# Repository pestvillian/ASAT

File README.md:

**Automated Sample Agitation Transportation System**

We are an Electrical Engineering Capstone group from the University of California, Santa Cruz. Our project aims to design a more efficient, more cost-effective solution for medical staff and researchers to process human samples for imaging. 

Here is an overview of the file structure:
  - Five folders for each group member
  - "Motor-Controller-Firmware" Firmware files for the motor controller motherboard and touchscreen daughterboard
  - "Motor-Controller-Board" contains PCB files for the Motor Controller PCB
  - "motor_tests" has test scripts for controlling the motors

Finally, we created a poster to visually explain our project!

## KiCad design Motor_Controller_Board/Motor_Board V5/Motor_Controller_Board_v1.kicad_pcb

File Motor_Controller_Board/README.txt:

List of changes to track progress.

4/17/25 9:55pm. Added TMC2226 stepper driver to schematic and followed the datasheet. left questions in the schematic. main concerns are vmotor filtering, do we need diagnostic pins like pdn_uart, diag and index, and what vsense resistors do we use? there are other smaller questions too. -Dorjee

4/17/25 11:42pm. made some small updates. vmotor basic filtering is two 100n decouple caps and one 100u bulk cap. they recommend low ESR caps, which provide faster response time. however, they also recommend voltage spikes to be delayed, which would imply high ESR caps would be good too? need to do more research

4/30/25. schematic rough draft is done. i need to revisions now to make sure it will actually work. there is a main page, buck page, microcontroller page, and a stepper driver page. 

5/2/25. revised schematic with Mishari and Alex. pretty confident in the design, so we started picking footprints. I've finished the microcontroller and stepper driver footprints, working on the buck regulators right now. i want to use the same 50V rated capacitor for both Cin and Cout.

5/3/25. all footprints assigned and every part manufacturer, manufacturer part number, and jcsc part number for BOM. added boot configuration for microcontroller. ready to begin premature layout, but still very open to changes in schematic.

5/3/25. added all 3d models and starting pcb layout. it is tricky

5/4/25. drastically simplified design by using 24V from SMPS for all motors. only one buck regulator for logic components. layout has begun and a general placement for parts has been established by myself without review from team yet. many changes can be made. stepper drivers likely will switch to +3.3V logic, vmotor filtering should be changed to surface mounts for size continuity, copy pasting the setup from one driver to the other two, and more. 

5/5/25. Reviewed schematic with Alex and Mishari. We are confident in the schematic, we will clean up a few last things tonight and then continue layout tomorrow.

5/5/25. placed all components in a rough outline, going to review with teammates tomorrow.

5/6/25. 75% of routing finished, but the routing was very sloppy.

5/7/25. pcb design is almost finished. Petersen was relatively happy with our layout and gave some tips. mishari will implement the tips tonight. no erc or drc errors currently except for the asats logo on the pcb layout. needs a final review tomorrow and then it will be ordered!

5/8/25. Mishari added bottom +24V plane instead of 2mm trace and was reviewed by team. Changed enable pins to be controlled by esp32. added potentiometer. alex, mishari and Dorjee all reviewed footprints and design. we plan to order tomorrow, will review tonight and tomorrow before ordering.

5/8/25. switched board to horizontal text and cleaned it up.

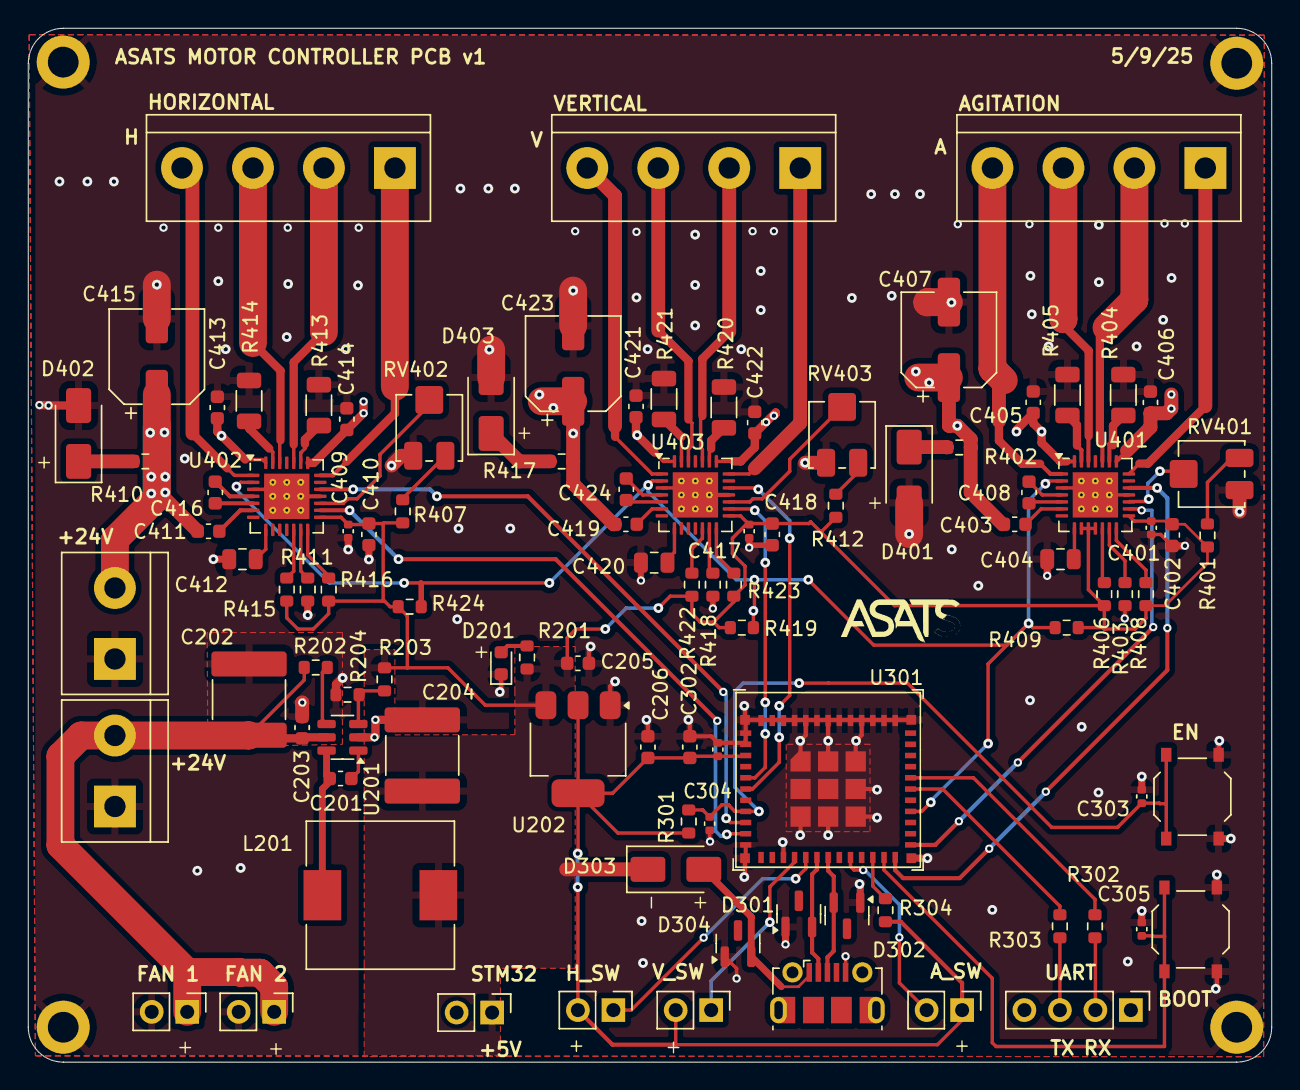
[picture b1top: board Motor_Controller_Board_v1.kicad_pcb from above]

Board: 2 copper layers, 89.0 x 74.0 mm, 104 parts (0 on the bottom side), 78 nets.

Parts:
C201, C203, C403, C405, C406, C408, C411, C413, C414, C416, C419, C421, C422, C424: 100n; C_0603_1608Metric
C202, C204: 22u; C_2220_5750Metric
C205, C206, C302, C402, C410, C418: 10u; C_0603_1608Metric
C301, C303, C305, C401, C409, C417: 100n; C_0402_1005Metric
C304: 1u; C_0402_1005Metric
C404, C412, C420: 220n; C_0805_2012Metric
C407, C415, C423: 100u; CP_Elec_6.3x7.7
D201: RED; LED_0603_1608Metric
D301, D302, D304: PSM712-LF-T7; SOT-23
D303: SS14; D_SMA
D401, D402, D403: SMAJ28A; D_SMA
H201, H202, H203, H204: MountingHole_Pad; MountingHole_2.2mm_M2_DIN965_Pad
J201, J203: Conn_01x02; TerminalBlock_bornier-2_P5.08mm
J202, J206, J207, J303, J304, J305: Conn_01x02; PinHeader_1x02_P2.54mm_Vertical
J301: Conn_01x04; PinHeader_1x04_P2.54mm_Vertical
J302: USB_B_Micro; USB_Micro-B_Molex-105017-0001
J401, J402, J403: Conn_01x04; TerminalBlock_bornier-4_P5.08mm
L201: 22u; L_10.4x10.4_H4.8
R201: 5k1; R_0603_1608Metric
R202, R408, R409, R416, R419, R423, R424: 100k; R_0603_1608Metric
R203: 68k; R_0603_1608Metric
R204: 13k; R_0603_1608Metric
R301, R304, R406, R415, R422: 10k; R_0603_1608Metric
R302, R303: 0R; R_0603_1608Metric
R401, R403, R407, R411, R412, R418: 24k; R_0603_1608Metric
R402, R410, R417: 10R; R_0603_1608Metric
R404, R405, R413, R414, R420, R421: 75m; R_1206_3216Metric
RV401, RV402, RV403: 10k; Potentiometer_Bourns_3314J_Vertical
SW301, SW302: SW_Push; SW_Push_1P1T_XKB_TS-1187A
U201: TP6841S6; SOT-23-6
U202: AMS1117; SOT-223-3_TabPin2
U301: ESP32-C6-MINI-1; ESP32-C6-MINI-1U
U401, U402, U403: A4988; QFN-28-1EP_5x5mm_P0.5mm_EP3.25x3.25mm_ThermalVias

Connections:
+3.3V: C206.1, C301.2, C302.1, J303.1, J304.2, J305.2, R301.1, R304.1, U202.2 (VO), U301.3 (3V3)
+5V: C204.1, C205.1, C401.2, C402.1, C409.2, C410.1, C417.2, C418.1, D303.1 (K), J202.1, L201.2, R201.2, R203.1, R401.2, R406.1, R407.2, R408.1, R409.1, R412.2, R415.1, R416.1, R419.1, R422.1, R423.1, R424.1, U202.3 (VI), U401.9 (MS1), U401.10 (MS2), U401.11 (MS3), U401.15 (VDD), U402.15 (VDD), U403.15 (VDD)
+24V: C403.2, C405.2, C406.2, C407.1, C411.2, C413.2, C414.2, C415.1, C419.2, C421.2, C422.2, C423.1, J203.2, R402.1, R410.1, R417.1, U401.22 (VBB1), U401.28 (VBB2), U402.22 (VBB1), U402.28 (VBB2), U403.22 (VBB1), U403.28 (VBB2)
/Microcontroller/+VBUS: D303.2 (A), D304.2 (A), J302.1 (VBUS)
/Microcontroller/AGITATION_SWITCH: J303.2, U301.20 (IO15)
/Microcontroller/BOOT: C305.2, SW302.2, U301.23 (IO9)
/Microcontroller/EN: C303.2, C304.1, R301.2, SW301.2, U301.8 (EN)
/Microcontroller/HORIZONTAL_SWITCH: J305.1, U301.16 (IO7)
/Microcontroller/IO8: R304.2, U301.22 (IO8)
/Microcontroller/RXD: J301.2, R302.2
/Microcontroller/RXD0: R303.1, U301.30 (RXD0)
/Microcontroller/TXD: J301.3, R303.2
/Microcontroller/TXD0: R302.1, U301.31 (TXD0)
/Microcontroller/USB_D+: D302.2 (A), J302.3 (D+), U301.18 (IO13)
/Microcontroller/USB_D-: D301.2 (A), J302.2 (D-), U301.17 (IO12)
/Microcontroller/VERTICAL_SWITCH: J304.1, U301.15 (IO6)
/Power Supply/BUCK_BST: C201.2, U201.1 (BST)
/Power Supply/BUCK_EN: R202.2, U201.4 (EN)
/Power Supply/BUCK_FB: R203.2, R204.2, U201.3 (FB)
/Power Supply/BUCK_SW: C201.1, L201.1, U201.6 (SW)
/Power Supply/DIGITAL_POWER_+24V: C202.1, C203.2, J201.2, J206.1, J207.1, R202.1, U201.5 (VIN)
/Stepper Drivers/AGITATE_1A: J401.2, U401.24 (OUT1A)
/Stepper Drivers/AGITATE_1B: J401.1, U401.21 (OUT1B)
/Stepper Drivers/AGITATE_2A: J401.3, U401.26 (OUT2A)
/Stepper Drivers/AGITATE_2B: J401.4, U401.1 (OUT2B)
/Stepper Drivers/A_CP1: C408.1, U401.4 (CP1)
/Stepper Drivers/A_CP2: C408.2, U401.5 (CP2)
/Stepper Drivers/A_FLYBACK: D401.1 (K), R402.2
/Stepper Drivers/A_POT_IN: R401.1, RV401.1
/Stepper Drivers/A_RESET: R406.2, U401.12 (~RESET)
/Stepper Drivers/A_ROSC: R403.2, U401.13 (ROSC)
/Stepper Drivers/A_SENSE1: R404.1, U401.23 (SENSE1)
/Stepper Drivers/A_SENSE2: R405.1, U401.27 (SENSE2)
/Stepper Drivers/A_SLEEP: R408.2, U401.14 (~SLEEP)
/Stepper Drivers/A_VCP: C403.1, U401.6 (VCP)
/Stepper Drivers/A_VREF: RV401.2, U401.17 (VREF)
/Stepper Drivers/A_VREG: C404.1, U401.8 (VREG)
/Stepper Drivers/HORIZONTAL_1A: J402.2, U402.24 (OUT1A)
/Stepper Drivers/HORIZONTAL_1B: J402.1, U402.21 (OUT1B)
/Stepper Drivers/HORIZONTAL_2A: J402.3, U402.26 (OUT2A)
/Stepper Drivers/HORIZONTAL_2B: J402.4, U402.1 (OUT2B)
/Stepper Drivers/H_CP1: C416.1, U402.4 (CP1)
/Stepper Drivers/H_CP2: C416.2, U402.5 (CP2)
/Stepper Drivers/H_FLYBACK: D402.1 (K), R410.2
/Stepper Drivers/H_POT_IN: R407.1, RV402.1
/Stepper Drivers/H_RESET: R415.2, U402.12 (~RESET)
/Stepper Drivers/H_ROSC: R411.2, U402.13 (ROSC)
/Stepper Drivers/H_SENSE1: R413.1, U402.23 (SENSE1)
/Stepper Drivers/H_SENSE2: R414.1, U402.27 (SENSE2)
/Stepper Drivers/H_SLEEP: R416.2, U402.14 (~SLEEP)
/Stepper Drivers/H_VCP: C411.1, U402.6 (VCP)
/Stepper Drivers/H_VREF: RV402.2, U402.17 (VREF)
/Stepper Drivers/H_VREG: C412.1, U402.8 (VREG)
/Stepper Drivers/VERTICAL_1A: J403.2, U403.24 (OUT1A)
/Stepper Drivers/VERTICAL_1B: J403.1, U403.21 (OUT1B)
/Stepper Drivers/VERTICAL_2A: J403.3, U403.26 (OUT2A)
/Stepper Drivers/VERTICAL_2B: J403.4, U403.1 (OUT2B)
/Stepper Drivers/V_CP1: C424.1, U403.4 (CP1)
/Stepper Drivers/V_CP2: C424.2, U403.5 (CP2)
/Stepper Drivers/V_FLYBACK: D403.1 (K), R417.2
/Stepper Drivers/V_POT_IN: R412.1, RV403.1
/Stepper Drivers/V_RESET: R422.2, U403.12 (~RESET)
/Stepper Drivers/V_ROSC: R418.2, U403.13 (ROSC)
/Stepper Drivers/V_SENSE1: R420.1, U403.23 (SENSE1)
/Stepper Drivers/V_SENSE2: R421.1, U403.27 (SENSE2)
/Stepper Drivers/V_SLEEP: R423.2, U403.14 (~SLEEP)
/Stepper Drivers/V_VCP: C419.1, U403.6 (VCP)
/Stepper Drivers/V_VREF: RV403.2, U403.17 (VREF)
/Stepper Drivers/V_VREG: C420.1, U403.8 (VREG)
AGITATION_DIR: U301.24 (IO18), U401.19 (DIR)
AGITATION_STEP: U301.25 (IO19), U401.16 (STEP)
DRIVER_ENABLE: R409.2, R419.2, R424.2, U301.28 (IO22), U401.2 (~ENABLE), U402.2 (~ENABLE), U403.2 (~ENABLE)
GND: C202.2, C203.1, C204.2, C205.2, C206.2, C301.1, C302.2, C303.1, C304.2, C305.1, C401.1, C402.2, C404.2, C405.1, C406.1, C407.2, C409.1, C410.2, C412.2, C413.1, C414.1, C415.2, C417.1, C418.2, C420.2, C421.1, C422.1, C423.2, D201.1 (K), D301.1 (K), D302.1 (K), D304.1 (K), D401.2 (A), D402.2 (A), D403.2 (A), H201.1, H202.1, H203.1, H204.1, J201.1, J202.2, J203.1, J206.2, J207.2, J302.5 (GND), R204.1, R403.1, R404.2, R405.2, R411.1, R413.2, R414.2, R418.1, R420.2, R421.2, RV401.3, RV402.3, RV403.3, SW301.1, SW302.1, U201.2 (GND), U202.1 (ADJ), U301.1 (GND), U301.2 (GND), U301.11 (GND), U301.14 (GND), U301.36 (GND), U301.37 (GND), U301.38 (GND), U301.39 (GND), U301.40 (GND), U301.41 (GND), U301.42 (GND), U301.43 (GND), U301.44 (GND), U301.45 (GND), U301.46 (GND), U301.47 (GND), U301.48 (GND), U301.49 (GND), U301.50 (GND), U301.51 (GND), U301.52 (GND), U301.53 (GND), U401.3 (GND), U401.18 (GND), U401.29 (GND), U402.3 (GND), U402.18 (GND), U402.29 (GND), U403.3 (GND), U403.18 (GND), U403.29 (GND)
HORIZONTAL_DIR: U301.9 (IO4), U402.19 (DIR)
HORIZONTAL_STEP: U301.10 (IO5), U402.16 (STEP)
unnamed: D201.2 (A), R201.1
VERTICAL_DIR: U301.6 (IO3), U403.19 (DIR)
VERTICAL_STEP: U301.5 (IO2), U403.16 (STEP)

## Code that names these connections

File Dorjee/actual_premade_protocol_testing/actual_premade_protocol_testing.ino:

/************
WHAT THIS CODE DOES, nvm its outdated
This is a simple test for sending data from the STM32 to the ESP32 via UART.
The STM32 sends two lines of data. The first line is a title and the second is the data.
The data is formatted as step type, # of repeats, mix speed, mix duration and dry time.
For example, "B9954" is bind step, 9 repeats, speed of 9, mix duration of 5, and dry time of 4.
The first line is ignored by using the startFlag and checking for a newline.
The startFlag is reset after the second line is terminated by the tab character.
*************/

#include "esp32-hal-timer.h"

hw_timer_t *timer = NULL;  // declaration of timer
static int dirTimerTicks = 0;
static int totalTimerTicks = 0;
// function call by the timer interruption
void IRAM_ATTR onTimer() {
  dirTimerTicks++;
  totalTimerTicks++;
}

const int AGITATION_STEP_PIN = 12;
const int AGITATION_DIR_PIN = 13;

const int VERTICAL_STEP_PIN = 27;
const int VERTICAL_DIR_PIN = 14;

const int HORIZONTAL_STEP_PIN = 25;
const int HORIZONTAL_DIR_PIN = 26;

#define MAX_LINE_LENGTH 32
#define MAX_LINES 100

// Initialize the tempBuffer with nulls ('\0')
char tempBuffer[MAX_LINES][MAX_LINE_LENGTH] = { { '\0' } };
uint8_t i = 0;
uint8_t j = 0;

void setup() {
  Serial.begin(115200);

  //agitation motor
  pinMode(AGITATION_DIR_PIN, OUTPUT);  // Set the pin as an output
  ledcAttachChannel(AGITATION_STEP_PIN, 5000, 8, 8);
  ledcWrite(AGITATION_STEP_PIN, 0);

  //vertical motor
  pinMode(VERTICAL_DIR_PIN, OUTPUT);  // Set the pin as an output
  ledcAttachChannel(VERTICAL_STEP_PIN, 100, 8, 9);
  ledcWrite(VERTICAL_STEP_PIN, 0);

  //horizontal motor
  pinMode(HORIZONTAL_DIR_PIN, OUTPUT);  // Set the pin as an output
  ledcAttachChannel(HORIZONTAL_STEP_PIN, 100, 8, 10);
  ledcWrite(HORIZONTAL_STEP_PIN, 0);

  //setup timer interrupt
  timer = timerBegin(1000000);
  timerAttachInterrupt(timer, &onTimer);
  if (timer == NULL) {
    Serial.println("Error with the start of the timer");
    while (1)
      ;
  }
  timerAlarm(timer, 10000, true, 0);  // 1000000 µs = 10ms = 0.01s
  timerStart(timer);

  //Fill in tempBuffer with premade protocol
  strcpy(tempBuffer[1], "A945");  //mix time, mix speed, mix depth
  strcpy(tempBuffer[2], "P5");
  strcpy(tempBuffer[3], "A563");
  //strcpy(tempBuffer[4], "B5");
  //strcpy(tempBuffer[5], "B8");

  Serial.println("Begin Test");
}

void loop() {

  //go line by line through tempBuffer and execute the protocol
  for (int a = 1; a < MAX_LINES; a++) {  //skip first line cuz it is the title
    //handle pause
    if (tempBuffer[a][0] == 'P') {
      pauseMotors(tempBuffer[a][1]);
    }
    //handle binding
    if (tempBuffer[a][0] == 'B') {
      //beingBinding(tempBuffer[1][1], tempBuffer[1][2]);
    }
    //handle agitation
    if (tempBuffer[a][0] == 'A') {
      startAgitating(tempBuffer[a][1], tempBuffer[a][2], tempBuffer[a][3]);
    }
  }
}

//pause the motor for specified time in milliseconds
void pauseMotors(char input_duration) {
  int intDuration = input_duration - '0';  //convert from ascii to int
  ledcWrite(AGITATION_STEP_PIN, 255);
  delay(intDuration * 1000);         //convert from seconds to milliseconds for delay function
  ledcWrite(AGITATION_STEP_PIN, 0);  //this is just for debugging to see the pause function bring the pin high and then low
}

//three timing constraints: total agitation time, direction switching time, acceleration time
void startAgitating(unsigned long mix_time, uint8_t mix_speed, uint8_t mix_depth) {
  //ascii to int conversions
  int int_mix_time = mix_time - '0';    //convert from ascii to int
  int int_mix_speed = mix_speed - '0';  //convert from ascii to int
  int int_mix_depth = mix_depth - '0';  //convert from ascii to int

  //map inputs to usable numbers
  int mix_time_ms = int_mix_time * 1000;  //get the mix_time in milliseconds
  int agitateStepFrequency = mapSpeedtoFreq(int_mix_speed);
  int agitateHalfPeriod = mapDepthtoTime(int_mix_depth);  //half period cuz thats what it is? what do i name this

  /** begin actual agitation process ***/

  //start the interrupt for chef time
  dirTimerTicks = 0;
  totalTimerTicks = 0;
  //timerRestart(timer);

  //get start time and start the motor up
  uint32_t curTime = millis();
  ledcChangeFrequency(AGITATION_STEP_PIN, 5000, 8);
  ledcWrite(AGITATION_STEP_PIN, 128);

  //stay in this agitation loop until the total agitation time is finished
  while ((millis() - curTime) < mix_time_ms) {
    if (dirTimerTicks == 10) {
      ledcChangeFrequency(12, 5000 + 500 * int_mix_speed / 3, 8);
    }
    if (dirTimerTicks == 20) {
      ledcChangeFrequency(12, 5000 + 500 * int_mix_speed * 2 / 3, 8);
    }
    if (dirTimerTicks == 30) {
      ledcChangeFrequency(12, 5000 + 500 * int_mix_speed, 8);
    }
    if (dirTimerTicks == agitateHalfPeriod - 20) {
      ledcChangeFrequency(12, 5000 + 500 * int_mix_speed * 2 / 3, 8);
    }
    if (dirTimerTicks == agitateHalfPeriod - 10) {
      ledcChangeFrequency(12, 5000 + 500 * int_mix_speed / 3, 8);
    }
    if (dirTimerTicks == agitateHalfPeriod) {
      ledcChangeFrequency(12, 5000, 8);
      digitalWrite(13, !digitalRead(13));
      dirTimerTicks = 0;
    }
  }
  //finished agitating, turn the motor off
  ledcWrite(AGITATION_STEP_PIN, 0);
}

int mapSpeedtoFreq(int input_speed) {
  int output_frequency = 5500 + input_speed * 500;  //input speed of 9 maxes out at 10khz
  return output_frequency;
}

int mapDepthtoTime(int input_depth) {
  int output_time = 55 + input_depth * 5;  //input depth of 9 maxes out at 100ms of movement. min depth is 55ms of movement
  return output_time;
}

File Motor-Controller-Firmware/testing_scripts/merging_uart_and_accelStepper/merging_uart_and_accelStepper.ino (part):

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const int MOTOR_Y_STEP_CHANNEL = 3;

//limit switches
const int AGITATION_SWITCH = 15;
const int VERTICAL_SWITCH = 6;
const int HORIZONTAL_SWITCH = 7;
AccelStepper stepper(AccelStepper::DRIVER, AGITATION_MOTOR_STEP, AGITATION_MOTOR_DIR);
ezButton limitSwitchY(VERTICAL_SWITCH);           // create ezButton object that attach to ESP32 pin GPIO6
ezButton limitSwitchX(HORIZONTAL_SWITCH);         // create ezButton object that attach to ESP32 pin GPIO7
ezButton limitSwitchAgitation(AGITATION_SWITCH);  // create ezButton object that attach to ESP32 pin GPIO15

//motor enable
const int MOTOR_ENABLE = 22;
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  limitSwitchY.setDebounceTime(50);

  //limit switches are pulled down. when pressed, they connect to vcc
  pinMode(HORIZONTAL_SWITCH, INPUT_PULLDOWN);
  pinMode(VERTICAL_SWITCH, INPUT_PULLDOWN);
  pinMode(AGITATION_SWITCH, INPUT_PULLDOWN);

  //motor direction pins are digital outputs
  pinMode(AGITATION_MOTOR_DIR, OUTPUT);
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
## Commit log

2025-02-13 first content
2025-02-13 fix file structure
2025-02-13 team filders readmes
2025-02-19 updateted prototype
2025-02-19 latest changes
2025-02-27 latest edits
2025-02-27 all!
2025-02-28 going to start using git now. current progress is the touchscreen has 10 pages, qr scanner uploads to any open slot
2025-02-28 first commit of control state machine on arduino ide. the parsing is working, but nothing else is working
2025-02-28 readme
2025-03-05 added basic protocoling queueing functionality
2025-03-07 can delete protocols now
2025-03-07 protocol Parsing Module Done
2025-03-08 working with uart
2025-03-13 updated UI
2025-04-03 rough outline of state machine using premade protocols. need to be tested tomorrow
2025-04-03 my changes
2025-04-03 agitate
2025-04-05 touchscreen works! also got the swd trace printing to work! going to start adding some buttons to sync up the touchscreen, lcd display and printing together.
2025-04-05 next and back buttons working. i have a lot of transferring code to do... this is good for tonight
2025-04-08 updated code for Alex to look at. i think the horizontal and vertical motor commands are working, but need to double check tomorrow
2025-04-08 basic functionalities of all 3 functions are working. turn vmotor on before vdd.
2025-04-10 SM updateds
2025-04-11 moving behavior done
2025-04-11 DAC CRACK
2025-04-11 digital
2025-04-12 The solution to agitation motor achieving top speed: accelerate it from a low frequency to goal frequency. the new issue is the agitation motor wont actually agitate properly. gonna start writing int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
2025-04-15 adding motor test files into this folder that correlate with a spreadsheet. row3 is the first test and it is smooth
2025-04-15 updates for 3 motors
2025-04-18 testing sharing kicad files. schematic currently has a rough microcontroller circuit. stepper driver and buck regulator pages need to be added
2025-04-18 trying to add .gitignore file
2025-04-18 trying a different file structure
2025-04-18 check the README. basically did rough draft of stepper motor section of schematic and need double checking
2025-04-18 small updates made to schematic. still need to continue reading the datasheet and understand the physics behind each decision made
2025-04-21 three new files. the one called clean is the onyl relevant file. it can run a premade protocol of multiple lines. need to test it on the actual motor tomorrow
2025-04-21 added an extremely crude bind function
2025-04-21 there was one typo. now it will compile and run the premade protocols. need to test with motor tomorrow
2025-04-21 the test_state_machine file works on the oscilloscope. need to test with actual motor, but that would come after the other files.
2025-04-21 get_num_protocols was written wrong... also the store protocol is also wrong. i have to fix this now, and this is changing a big part of the program flow. i will save this wrong file here.
2025-04-21 seemingly fixed it. didnt have to rewrite everything. the issue lied in the way the protocols were being deleted. simplified everything by just rewriting the delete function to shift all protocols in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
2025-04-21 the protocol storage function was wonky. i simplified it and fixed it. just remember that flash memory has 0xFF and the arrays we create are nulls. that is a headache to deal with, but its whatever
2025-04-21 a4988 working base code
2025-04-22 Gantry Head / AccelStepper / UI Working
2025-04-23 prototype works
2025-04-25 faster, but still not fast enough. keep tweaking the timestep, frequency, microstep, and maybe voltage. also vref can be possible because it seems low
2025-04-30 added debouncing and verified on oscilloscope that light finger touches are noisy.
2025-05-01 still dont know if these files can even be accessed, but the rough draft of schematic is finished. it needs revision to verify it will actually work. i made a top level page with three supporting pag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
2025-05-03 picking footprints. still need buck regulator footprints
2025-05-04 schematic and footprints have been selected. ready to start layout, but always open to changes in schematic
2025-05-04 changed jcsc to lcsc
2025-05-04 added 3d models. starting layout, it is hard
2025-05-05 design has been greatly simplified to only one buck regulator for logic components. smps will power the motors. layout has begun and a general component placement is done. needs to be reviewed by tea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
2025-05-06 discussed with Alex and Mishari. confident in schematic, going to do layout tomorrow
2025-05-06 general placement done. discuss with teammates tomorrow
2025-05-06 limit switch integration
2025-05-07 routing 75% finished, but very sloppy
2025-05-08 the file is called motor_controller_v3 because me and mishari have been trading files on google drive. almost finished with layout, mishari will implement petersen's advice and then tomorrow will be 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
2025-05-08 updated readme. i need to save everytime i want it to update
2025-05-08 all local changes Limit Switch FUll integration!!!!!
2025-05-09 testing new ballscrew
2025-05-09 Mishari added bottom +24V plane instead of 2mm trace and was reviewed by team. Changed enable pins to be controlled by esp32. added potentiometer. alex, mishari and Dorjee all reviewed footprints and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
2025-05-09 cleaned up board and switched to horizontal text
2025-05-10 done. see readme for update log
2025-05-14 fixing Agitation w AccelStepper
2025-05-15 State Machine Functional with Protocols
2025-05-16 Full SM Working New PCB
2025-05-16 new pcb works with prototypes, but agitation driver gets hot
2025-05-16 added a progress page and getting ready for uart to be sent to motor controller board. need to test this code tomorrow
2025-05-16 merged the old uart script for the prototype and greg's new script with accelstepper. gonna test this code tomorrow with the motor controller pcb
2025-05-16 used the debugger to check output of touchscreen. everything seems clean including the queue function. however, i used printf, and HAL_UART might be different
2025-05-17 touchscreen is integrated. functionality is still very messy. queue doesnt work, but i think if i add a newline char to the filler line it will work.
2025-05-17 cleaned up code
2025-05-18 touchscreen works with the esp32. queue is seemingly working, stop function is working, and data of the protocol appears crudely on the touchscreen. there seems to be issues with the limit switch not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
2025-05-19 App work
2025-05-20 3d Prints
2025-05-20 motors should turn off after protocol now
2025-05-20 app works less
2025-05-21 added the poster
2025-05-21 added readme for my own folder and cleaned it up
2025-05-21 App design work
2025-05-21 the app testing is working
2025-05-21 agitation now contains the pause section and has repeatibility. its lowk stable rn
2025-05-22 agitation always goes up now. its pretty stable
2025-05-22 this touchscreen has a timer that counts down, but it refresh the whole page. gonna fix that tomorrow
2025-05-23 agitation is functional. magnetize is functional. the vertical level isnt quite right, lots of bugs still. gonna run full protocol maybe tomorrow
2025-05-23 newApp kivy_UI3.0
2025-05-25 motors dont hit the test tray when going laterlly anymore. it seemed to have been an issue with either the autohome not using the bump method to home the agitation motor, using float values for magne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
2025-05-26 added file path
2025-05-27 fixed directory saving issue
2025-05-27 fixed 0 padding. packed app in dist
2025-05-28 fixed QR code with \r
2025-05-29 two changes: altium folder has new touchscreen redesign with qr scanner and fan controlled by mosfet and 2-layer board, still needs finishing touches. motor script is very stable right now, needs mor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
2025-05-29 almost done. just needs a final check from mishari, me and maybe alex. we are ordering for sure tomorrow!
2025-06-01 touchscreen seems stable but a few random glitches. the motors seem stable as well. there is some weird issues when an invalid protocol is sent. stilll need more testing, but honestly im almost conte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
2025-06-04 motors didnt really change. touchscreen is more stable now. i really only need the time left for the progress screen. the info button for protocols might be kind of tricky. gamze isnt even gonna use 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
2025-06-11 final code for esp32 and stm32 in the firmware folder. touchscreen pcb v1 and v2 uploaded in a new folder. project is stable and ready to be handed off to gamze
2025-06-11 cleaned up file names and readme
2025-06-23 used differential pairs for usb, changing mounting holes to be grounded, and removed esd diodes to get better via placements for usb return paths. havent tested it yet
2025-06-24 yooo i fixed the qr scanner. it actually works. im not sure if its charging, but it almost certainly is. im still not sure which of three fixes i did actually made the difference. its probably the gr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
2025-06-30 Created readme for firmware directory
